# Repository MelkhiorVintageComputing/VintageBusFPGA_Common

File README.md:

# VintageBusFPGA_Common
Common stuff for [SBusFPGA](https://github.com/rdolbeau/SBusFPGA), [NuBusFPGA](https://github.com/rdolbeau/NuBusFPGA)

## Content

* goblin_fb.py: 'Goblin', a Framebuffer (bit-mapped graphic display), supporting 1/2/4/8/16/32 bit depth, a single hardwired resolution to the screen, and windowboxed lower resolution. Also uses fb_dma.py (to read the framebuffer content from a LiteDRAM controller) and fb_video.py (timing generator). Originally based on Litex's own framebuffer code.

* goblin_accel.py: acceleration engine for the 'Goblin' framebuffer. Basically a custom VexRiscv core (VexRiscv_GoblinAccel_NuBus.v or VexRiscv_GoblinAccel_SBus.v) and some firmware (the blit_goblin*.* files).

* cdc_wb.py: a custom wrapper around [alexforencich's wb_async_reg.v](https://github.com/alexforencich/verilog-wishbone/blob/master/rtl/wb_async_reg.v), a Wishbone DCD component. Feature a customizable time-out to avoir the fast side overloading the slow side (a bit hackish but it works for my use case).

* fpga_blk_dma.py: a block DMA between a LIteSDRAM port and a set of FIFOs. Used to create burst (SBus) or block (NUbus) accesses from the device to the host memory. Used by RAM-based "disks".

* wb_master.py: A small Wishbone master (originally from enjoy-gigital) that can do basic read/write/wait commands. Used to configure the DDR3 controller w/o firmware.

* FLASH+TEMP-PMOD: a PMod-like module with a SPI NOR Flash device & a I2C temperature sensor. Can be used with the SBusFPGA were both feature are supported. On NuBusFPGA currently the I2C bus is not supported in MacOS. The Flash is currently usable to store the ROM for the device (Forth code for SBusFPGA, Declaration ROM for NuBusFPGA). The temperature sensor is supported in NetBSD 9.0 in SBusFPGA.

* PI2PMODSPI: a simple PCB to route the SPI bus from a Raspberry Pi to the appropriate pins on the FLASH+TEMP-PMOD above. Makes it easier to program the Flash NOR in the PMod with 'flashrom' on a Raspberry Pi.

## Not included:

* Other framebuffers: SBusFPGA has other framebuffers (1-bit bw2, 8-bit cg3, accelerated 8-bit cg6) that 'emaulate' (in a limited way) vintage framebuffers. SBus-specific.

* TRNG: a small True Random Number Generator, based on an old version of the neorv32's trng. Should be moved here, currently only in SBusFPGA.

* USB: Dolu1990's OHCI USB controller & standard Litex wrapper.

* SDRAM: standard LiteDRAM controller.

* Crypto engine: a very customized version of the Betrusted.IO crypto engine, featuring AES and GCM support and a Load/Store unit. Should be moved here, currently only in SBusFPGA.

* sdcard: standard LiteSDCard controller.

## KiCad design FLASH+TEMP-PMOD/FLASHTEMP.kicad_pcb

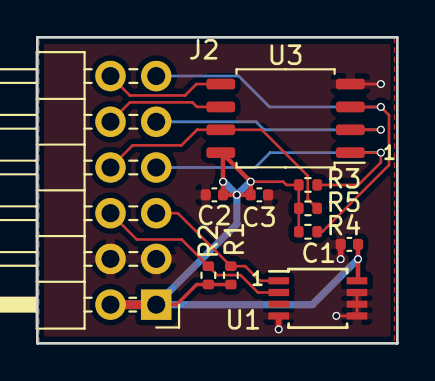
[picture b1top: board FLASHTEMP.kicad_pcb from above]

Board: 2 copper layers, 20.0 x 17.0 mm, 11 parts (0 on the bottom side), 10 nets.

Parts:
C1: 10nF 0402; C_0402_1005Metric
C2: 100nF 0402; C_0402_1005Metric
C3: 1uF 0402; C_0402_1005Metric
J2: Conn_02x06_Odd_Even; PinHeader_2x06_P2.54mm_Horizontal
R1, R2, R3, R4, R5: 5.6k 0402; R_0402_1005Metric
U1: PCT2075DP; TSSOP-8_3x3mm_P0.65mm_ForSeeedStudio
U3: W25Q128JVS; SOIC-8_5.23x5.23mm_P1.27mm

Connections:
+3V3: C1.1, C2.1, C3.1, J2.1, J2.2, R1.2, R2.2, R3.2, R4.2, R5.2, U1.8, U3.8
FLASH_CSn: J2.7, R3.1, U3.1
FLASH_SCLK: J2.10, U3.6
FLASH_SIO0: J2.12, U3.5
FLASH_SIO1: J2.9, U3.2
FLASH_SIO2: J2.11, R4.1, U3.3
FLASH_SIO3: J2.8, R5.1, U3.7
GND: C1.2, C2.2, C3.2, J2.3, J2.4, U1.4, U1.5, U1.6, U1.7, U3.4
I2C0_SCL: J2.6, R2.1, U1.2
I2C0_SDA: J2.5, R1.1, U1.1

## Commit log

2022-10-31 moved files from SBusFPGA
2022-10-31 more common files
2022-10-31 rename to avoid name conflict
2022-10-31 add fb_dma, fb_video to common
2022-10-31 add the blk dma to common
2022-10-31 add blit_goblin to common
2022-10-31 missing file
2022-10-31 more files moved to common
2022-10-31 ignore
2022-10-31 move Vex cores to common
2022-11-01 fix path (still very local...)
2022-11-04 swap b & r for newer Litex/HDMI
2022-11-18 add description
2022-11-18 more details
2022-11-18 links
2022-12-20 preliminary support for the hdl-util/hdmi contorller as an alternative
2023-01-08 first draft at audio-in-hdmi
2023-01-10 8-bits support
2023-01-11 HW mono support
2023-01-29 fix path to hdl-util_hdmi
2023-04-10 comments, disable LEDs
2023-04-10 remove dependency on Zbt-supporting compilers
2023-04-10 move Scala file for CG6/Goblin acceleration into Common
2023-05-08 add flash+temp pmod
    typo
2023-05-08 add PI2PMODSPI
2023-07-23 various debug blocks
2023-08-01 start mering patcher
2023-08-01 preliminary RAM expansion patch
2023-08-01 clean Makefiles
2023-08-01 readme
2023-09-16 license
2023-09-23 cleanup
2023-09-23 move DeclRom from NuBusFPGA to common
2023-09-23 typos
2023-10-12 flashsend for ZTex
2023-10-12 Makefile fix, add some HW info in HDMIAudio RSRC for the driver
2023-10-14 minor fixes to flashsend, resetFpga seems needed between plugin the board & using the flash
2023-10-22 improve #if's
2023-11-18 move some of board platform stuff to common
2023-11-18 start factorizing Mac stuff
2023-11-18 script to check if sdram init is messed up
2023-11-18 more stuff
2023-11-18 oups
2023-11-18 common sdram_init
2023-11-18 add goblin to common
2023-11-18 typo
2023-11-18 oups python....
2023-11-18 more oups python....
2023-12-02 make sector # configurable
2024-01-02 disable non-working sdcard by default
2024-01-02 fix non-alt hdmi phy
2024-02-11 fix partial and indexed LUT update
2024-02-17 updated ROM for automated makefile paramters, settable pixel clock
2024-02-17 ignore comma
2024-02-17 some hypothetical V2.0 support
2024-02-17 added 1024x768, 65 MHz clock
2024-02-23 no second res for alt phy, order resources in numerical order
2024-02-23 tested
2024-05-18 LC32FPGA, board-based name
2025-06-28 ROM patch to support 128 MiB in the 3/160 ROM (tested in TME only)
2025-06-28 readme for sun 3/160 memory
2025-06-28 add checksum
2025-06-28 Sun 3/60 ROM patch for extra memory
2025-06-28 add sun3 checksumming helper
2025-07-19 add a Sun3_60NoParity preliminary patch (untested)
2025-07-20 yet another trial: don't initialize/dtect keyboard in sys/rest;c::monreset()
2025-08-24 bypass less code, so we retain the memory sizing...
2025-09-24 missing checksum
2025-09-28 Patch to Rev R Sun-2 boot rom to speed up booting in simulation
2025-10-05 also change the UART 'time const' value (stored in usecmd.c::uart_init) to adapt to a different UART clock
2025-10-05 add test ROM for simulation, removing some costly delays
2025-11-05 add FIFO-based WB CDC
2026-03-25 DDR2 support in HW init
2026-03-25 use right array
2026-03-25 support DDR2-based board
2026-03-28 0x for hexa
2026-03-28 also geenrate .bit.bin for ztex
